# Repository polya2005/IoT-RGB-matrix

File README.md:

# IoT-RGB-matrix

## Functionalities

- Sending custom images (and animations) over WiFi to the display.
- Automatically generate a QR code for display (one application is to rickroll people)
- Serving as a "status" display like date/time, weather, etc.

## Project Components

- 40x40 RGB LED matrix, which is broken down into 25 PCBs of 8x8 matrix
- A control board, which is likely a Raspberry Pi Zero W

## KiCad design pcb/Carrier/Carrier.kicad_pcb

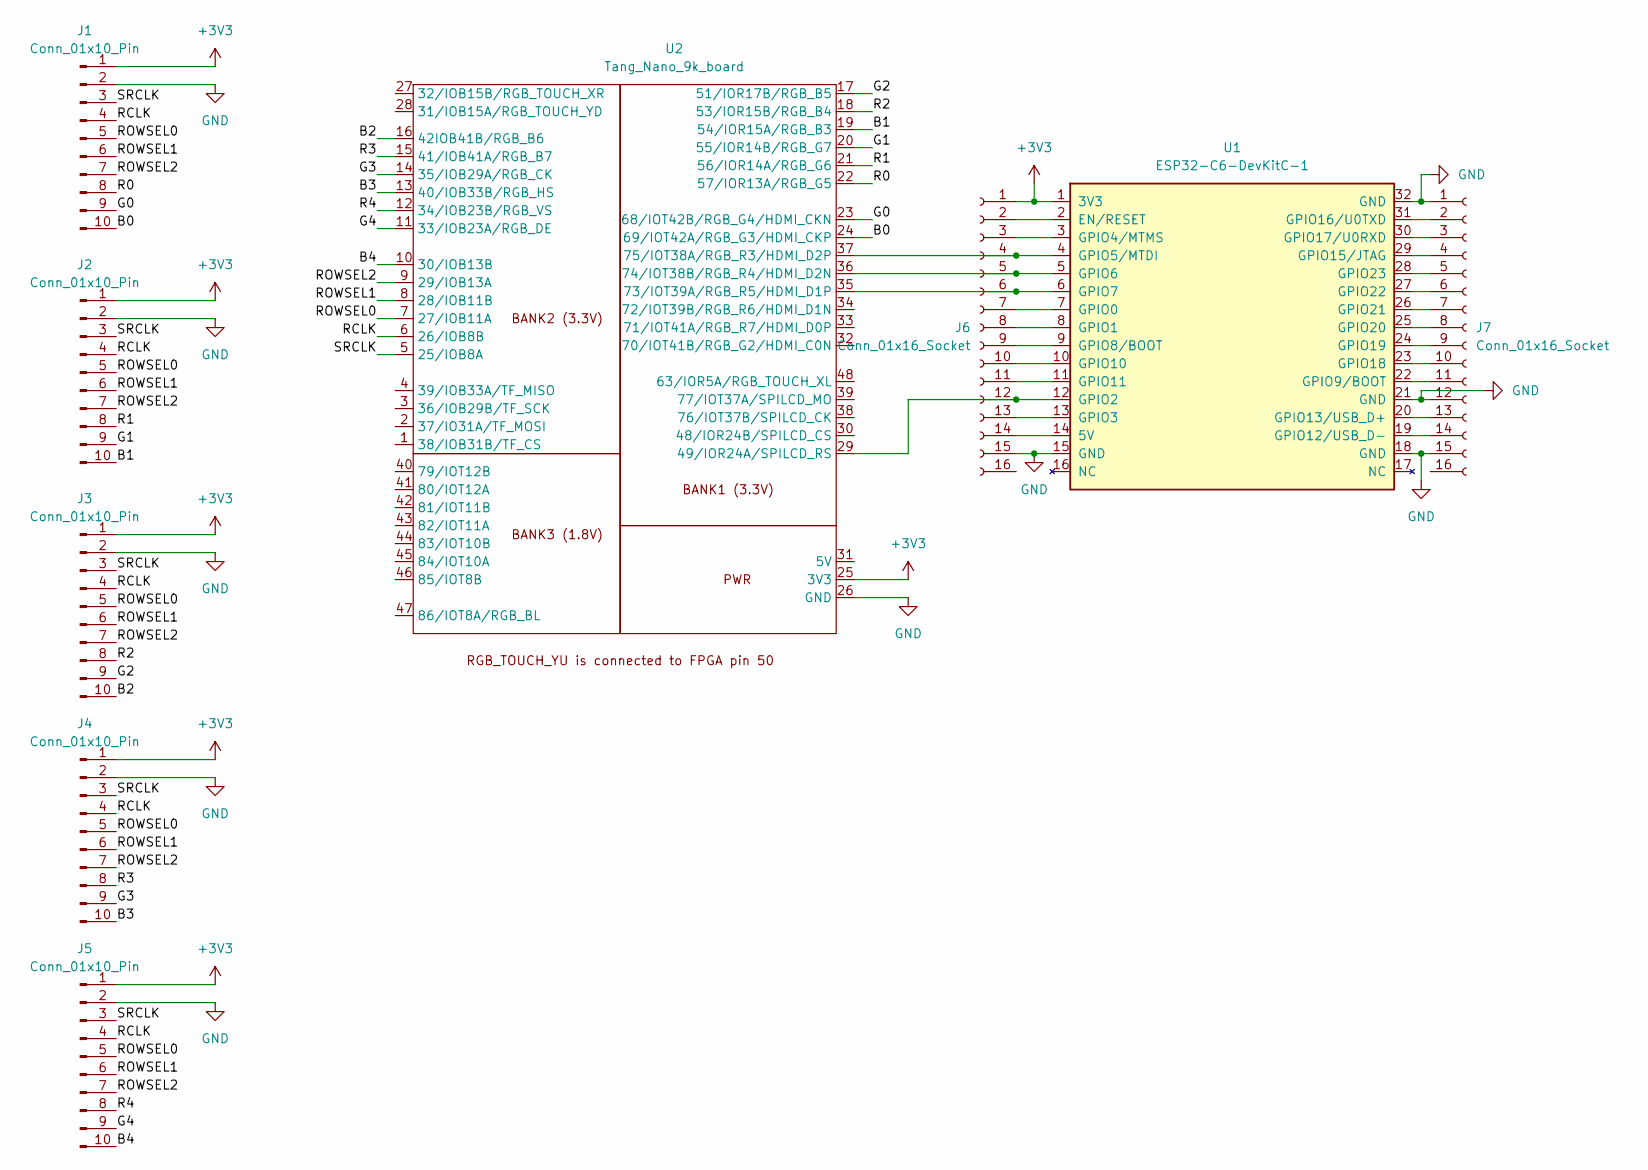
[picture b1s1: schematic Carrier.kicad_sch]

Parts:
J1, J2, J3, J4, J5: Conn_01x10_Pin; PinHeader_1x10_P2.54mm_Vertical
J6, J7: Conn_01x16_Socket; PinSocket_1x16_P2.54mm_Vertical
U1: ESP32-C6-DevKitC-1
U2: Tang_Nano_9k_board; Tang Nano 9K

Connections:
+3V3: J1.1, J2.1, J3.1, J4.1, J5.1, J6.1, U1.1 (3V3), U2.25 (3V3)
/B0: J1.10, U2.24 (69/IOT42A/RGB_G3/HDMI_CKP)
/B1: J2.10, U2.19 (54/IOR15A/RGB_B3)
/B2: J3.10, U2.16 (42IOB41B/RGB_B6)
/B3: J4.10, U2.13 (40/IOB33B/RGB_HS)
/B4: J5.10, U2.10 (30/IOB13B)
/G0: J1.9, U2.23 (68/IOT42B/RGB_G4/HDMI_CKN)
/G1: J2.9, U2.20 (55/IOR14B/RGB_G7)
/G2: J3.9, U2.17 (51/IOR17B/RGB_B5)
/G3: J4.9, U2.14 (35/IOB29A/RGB_CK)
/G4: J5.9, U2.11 (33/IOB23A/RGB_DE)
/R0: J1.8, U2.22 (57/IOR13A/RGB_G5)
/R1: J2.8, U2.21 (56/IOR14A/RGB_G6)
/R2: J3.8, U2.18 (53/IOR15B/RGB_B4)
/R3: J4.8, U2.15 (41/IOB41A/RGB_B7)
/R4: J5.8, U2.12 (34/IOB23B/RGB_VS)
/RCLK: J1.4, J2.4, J3.4, J4.4, J5.4, U2.6 (26/IOB8B)
/ROWSEL0: J1.5, J2.5, J3.5, J4.5, J5.5, U2.7 (27/IOB11A)
/ROWSEL1: J1.6, J2.6, J3.6, J4.6, J5.6, U2.8 (28/IOB11B)
/ROWSEL2: J1.7, J2.7, J3.7, J4.7, J5.7, U2.9 (29/IOB13A)
/SRCLK: J1.3, J2.3, J3.3, J4.3, J5.3, U2.5 (25/IOB8A)
GND: J1.2, J2.2, J3.2, J4.2, J5.2, J6.15, J7.1, J7.12, J7.15, U1.15 (GND), U1.18 (GND), U1.21 (GND), U1.32 (GND), U2.26 (GND)
unnamed: J6.2, U1.2 (EN/RESET)
unnamed: J6.3, U1.3 (GPIO4/MTMS)
unnamed: J6.4, U1.4 (GPIO5/MTDI), U2.37 (75/IOT38A/RGB_R3/HDMI_D2P)
unnamed: J6.5, U1.5 (GPIO6), U2.36 (74/IOT38B/RGB_R4/HDMI_D2N)
unnamed: J6.6, U1.6 (GPIO7), U2.35 (73/IOT39A/RGB_R5/HDMI_D1P)
unnamed: J6.7, U1.7 (GPIO0)
unnamed: J6.8, U1.8 (GPIO1)
unnamed: J6.9, U1.9 (GPIO8/BOOT)
unnamed: J6.10, U1.10 (GPIO10)
unnamed: J6.11, U1.11 (GPIO11)
unnamed: J6.12, U1.12 (GPIO2), U2.29 (49/IOR24A/SPILCD_RS)
unnamed: J6.13, U1.13 (GPIO3)
unnamed: J6.14, U1.14 (5V)
unnamed: J7.2, U1.31 (GPIO16/U0TXD)
unnamed: J7.3, U1.30 (GPIO17/U0RXD)
unnamed: J7.4, U1.29 (GPIO15/JTAG)
unnamed: J7.5, U1.28 (GPIO23)
unnamed: J7.6, U1.27 (GPIO22)
unnamed: J7.7, U1.26 (GPIO21)
unnamed: J7.8, U1.25 (GPIO20)
unnamed: J7.9, U1.24 (GPIO19)
unnamed: J7.10, U1.23 (GPIO18)
unnamed: J7.11, U1.22 (GPIO9/BOOT)
unnamed: J7.13, U1.20 (GPIO13/USB_D+)
unnamed: J7.14, U1.19 (GPIO12/USB_D-)

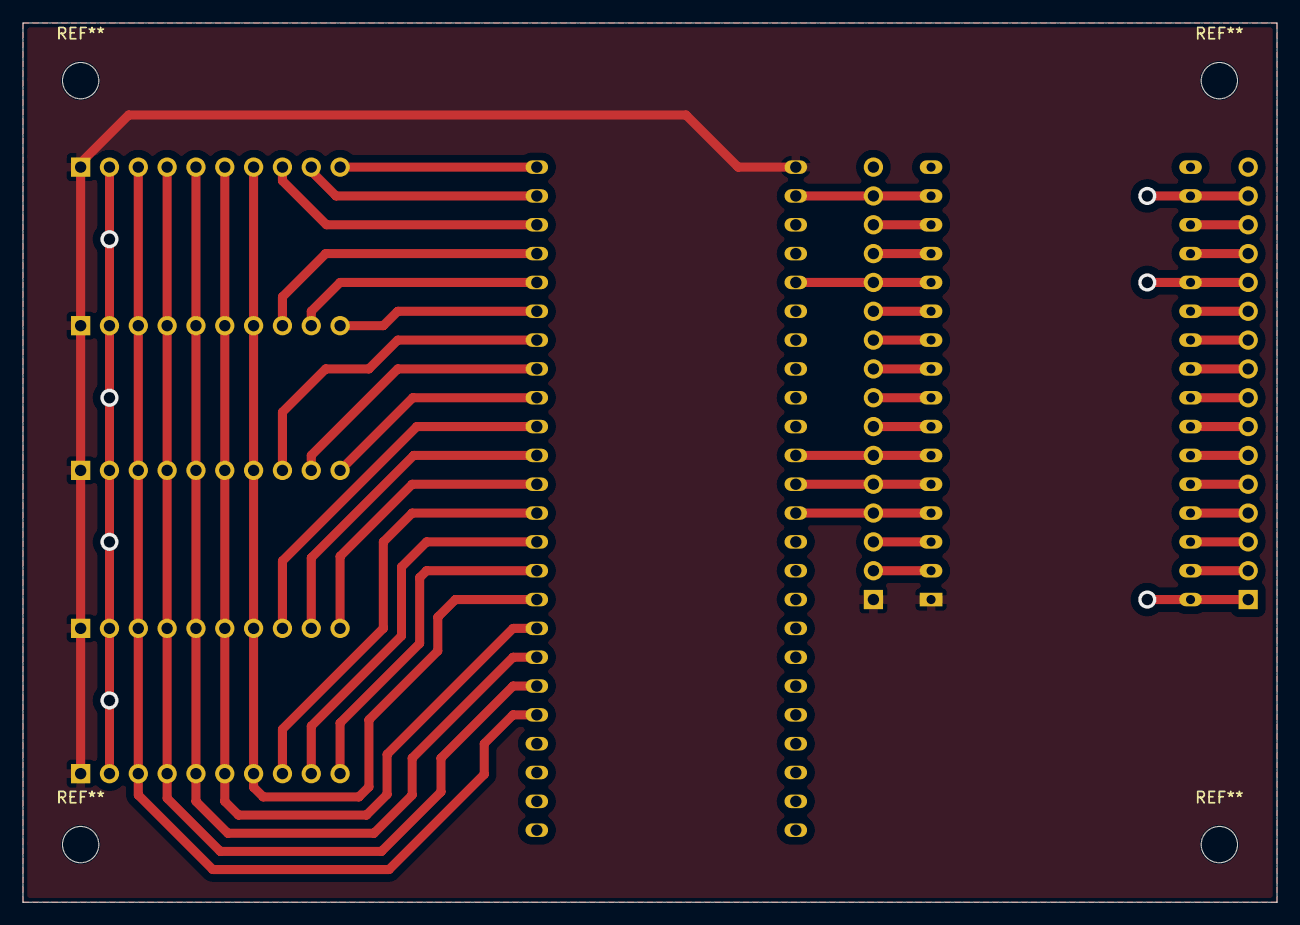
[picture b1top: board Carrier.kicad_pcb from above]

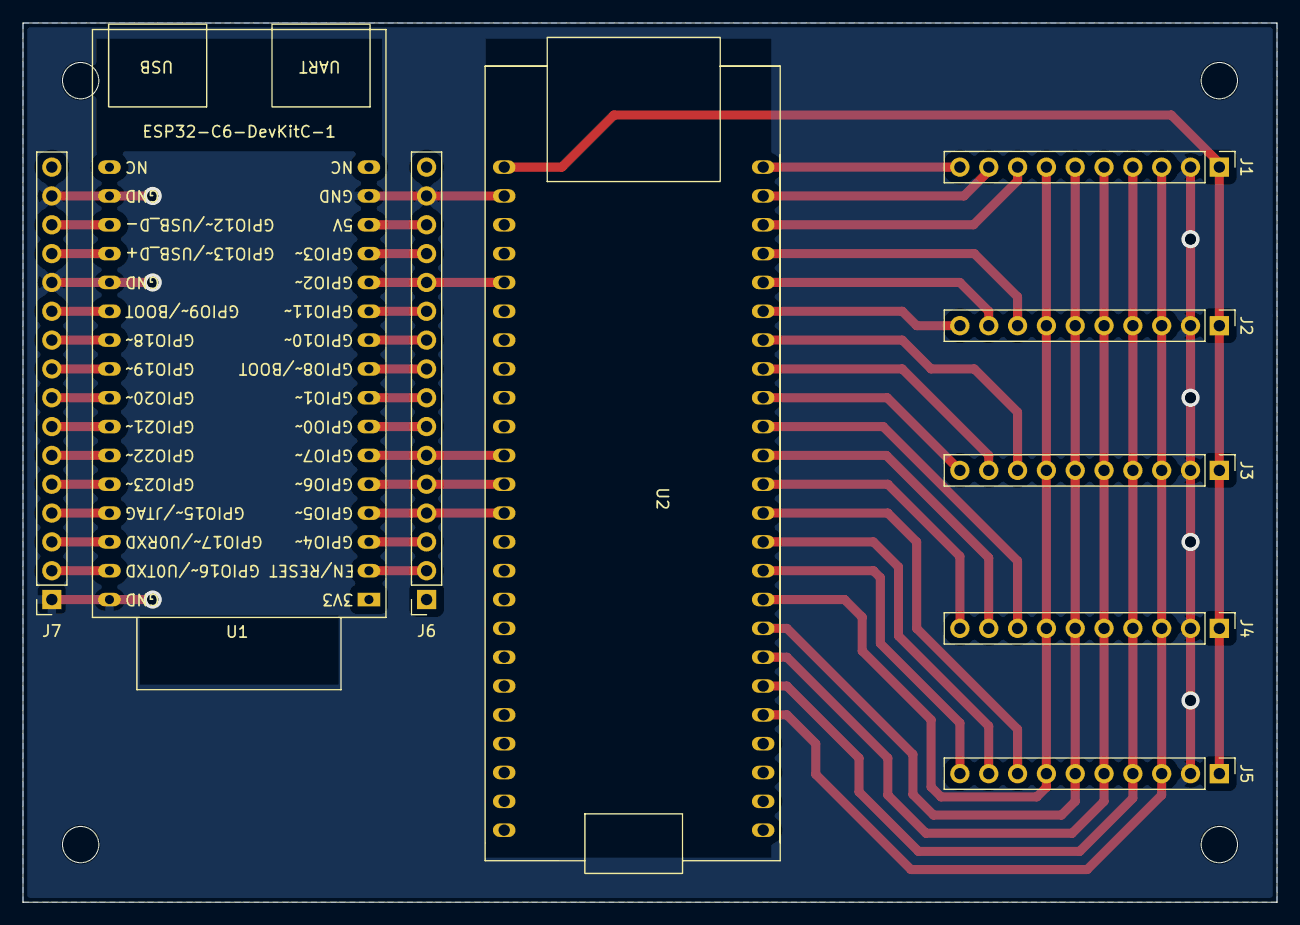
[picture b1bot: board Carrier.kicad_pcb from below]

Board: 2 copper layers, 110.5 x 77.5 mm, 9 parts (9 on the bottom side), 47 nets.

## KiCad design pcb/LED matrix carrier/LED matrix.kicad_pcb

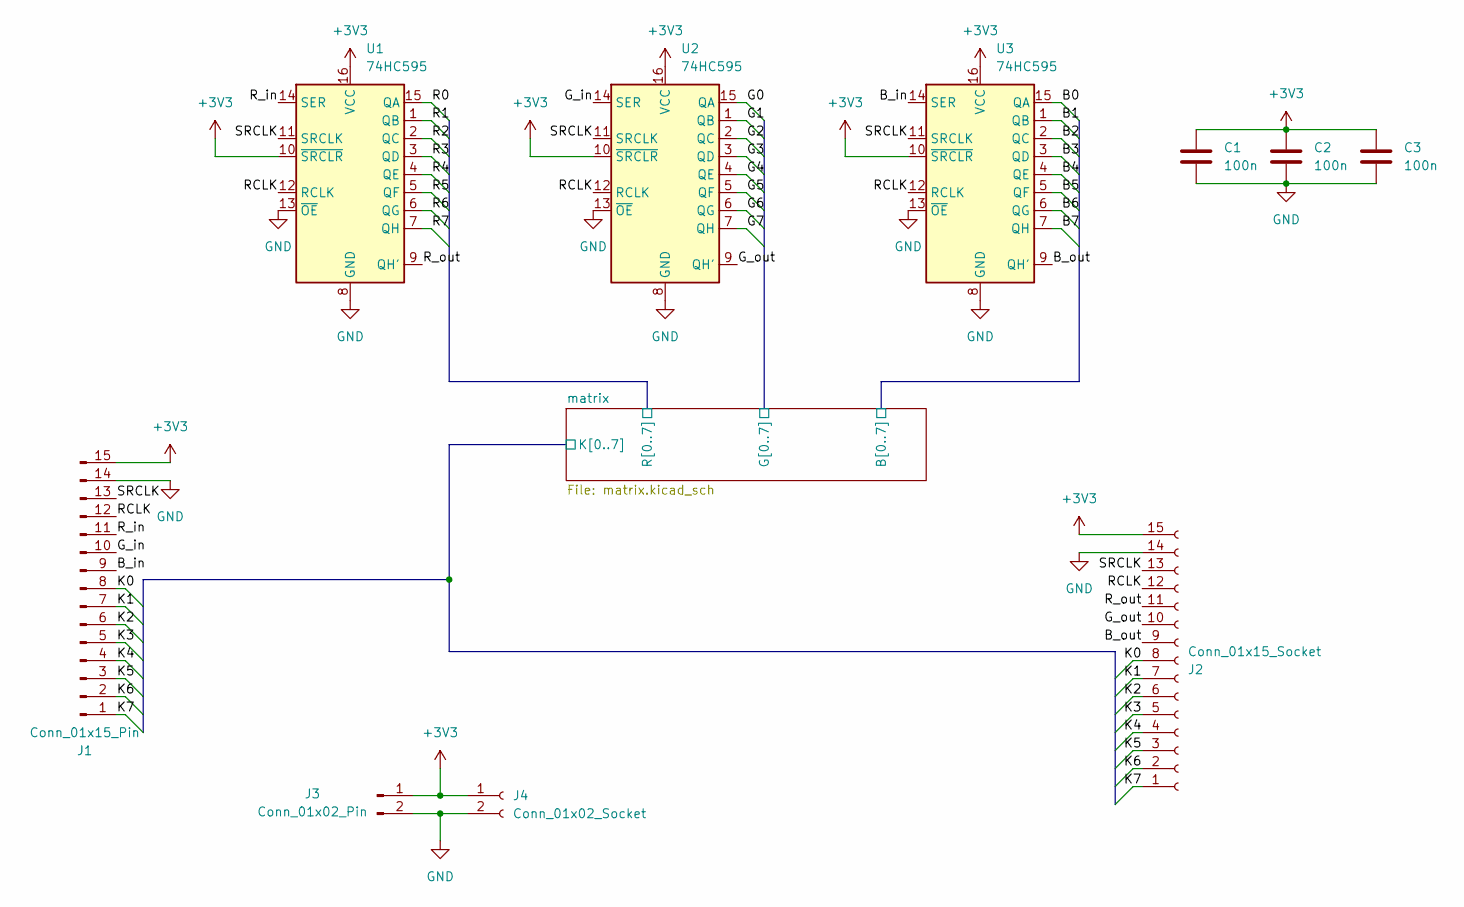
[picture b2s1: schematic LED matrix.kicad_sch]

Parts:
C1, C2, C3: 100n; C_1206_3216Metric_Pad1.33x1.80mm_HandSolder
J1: Conn_01x15_Pin; PinHeader_1x15_P2.54mm_Horizontal
J2: Conn_01x15_Socket; PinSocket_1x15_P2.54mm_Horizontal
J3: Conn_01x02_Pin; PinHeader_1x02_P2.54mm_Horizontal
J4: Conn_01x02_Socket; PinSocket_1x02_P2.54mm_Horizontal
U1, U2, U3: 74HC595; TSSOP-16_4.4x5mm_P0.65mm

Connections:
+3V3: C1.1, C2.1, C3.1, J1.15, J2.15, J3.1, J4.1, U1.10 (~SRCLR), U1.16 (VCC), U2.10 (~SRCLR), U2.16 (VCC), U3.10 (~SRCLR), U3.16 (VCC)
/B_in: J1.9, U3.14 (SER)
/B_out: J2.9, U3.9 (QH')
/G_in: J1.10, U2.14 (SER)
/G_out: J2.10, U2.9 (QH')
/RCLK: J1.12, J2.12, U1.12 (RCLK), U2.12 (RCLK), U3.12 (RCLK)
/R_in: J1.11, U1.14 (SER)
/R_out: J2.11, U1.9 (QH')
/SRCLK: J1.13, J2.13, U1.11 (SRCLK), U2.11 (SRCLK), U3.11 (SRCLK)
/matrix/B0: U3.15 (QA); also elsewhere on the board
/matrix/B1: U3.1 (QB); also elsewhere on the board
/matrix/B2: U3.2 (QC); also elsewhere on the board
/matrix/B3: U3.3 (QD); also elsewhere on the board
/matrix/B4: U3.4 (QE); also elsewhere on the board
/matrix/B5: U3.5 (QF); also elsewhere on the board
/matrix/B6: U3.6 (QG); also elsewhere on the board
/matrix/B7: U3.7 (QH); also elsewhere on the board
/matrix/G0: U2.15 (QA); also elsewhere on the board
/matrix/G1: U2.1 (QB); also elsewhere on the board
/matrix/G2: U2.2 (QC); also elsewhere on the board
/matrix/G3: U2.3 (QD); also elsewhere on the board
/matrix/G4: U2.4 (QE); also elsewhere on the board
/matrix/G5: U2.5 (QF); also elsewhere on the board
/matrix/G6: U2.6 (QG); also elsewhere on the board
/matrix/G7: U2.7 (QH); also elsewhere on the board
/matrix/K0: J1.8, J2.8; also elsewhere on the board
/matrix/K1: J1.7, J2.7; also elsewhere on the board
/matrix/K2: J1.6, J2.6; also elsewhere on the board
/matrix/K3: J1.5, J2.5; also elsewhere on the board
/matrix/K4: J1.4, J2.4; also elsewhere on the board
/matrix/K5: J1.3, J2.3; also elsewhere on the board
/matrix/K6: J1.2, J2.2; also elsewhere on the board
/matrix/K7: J1.1, J2.1; also elsewhere on the board
/matrix/R0: U1.15 (QA); also elsewhere on the board
/matrix/R1: U1.1 (QB); also elsewhere on the board
/matrix/R2: U1.2 (QC); also elsewhere on the board
/matrix/R3: U1.3 (QD); also elsewhere on the board
/matrix/R4: U1.4 (QE); also elsewhere on the board
/matrix/R5: U1.5 (QF); also elsewhere on the board
/matrix/R6: U1.6 (QG); also elsewhere on the board
/matrix/R7: U1.7 (QH); also elsewhere on the board
GND: C1.2, C2.2, C3.2, J1.14, J2.14, J3.2, J4.2, U1.8 (GND), U1.13 (~OE), U2.8 (GND), U2.13 (~OE), U3.8 (GND), U3.13 (~OE)

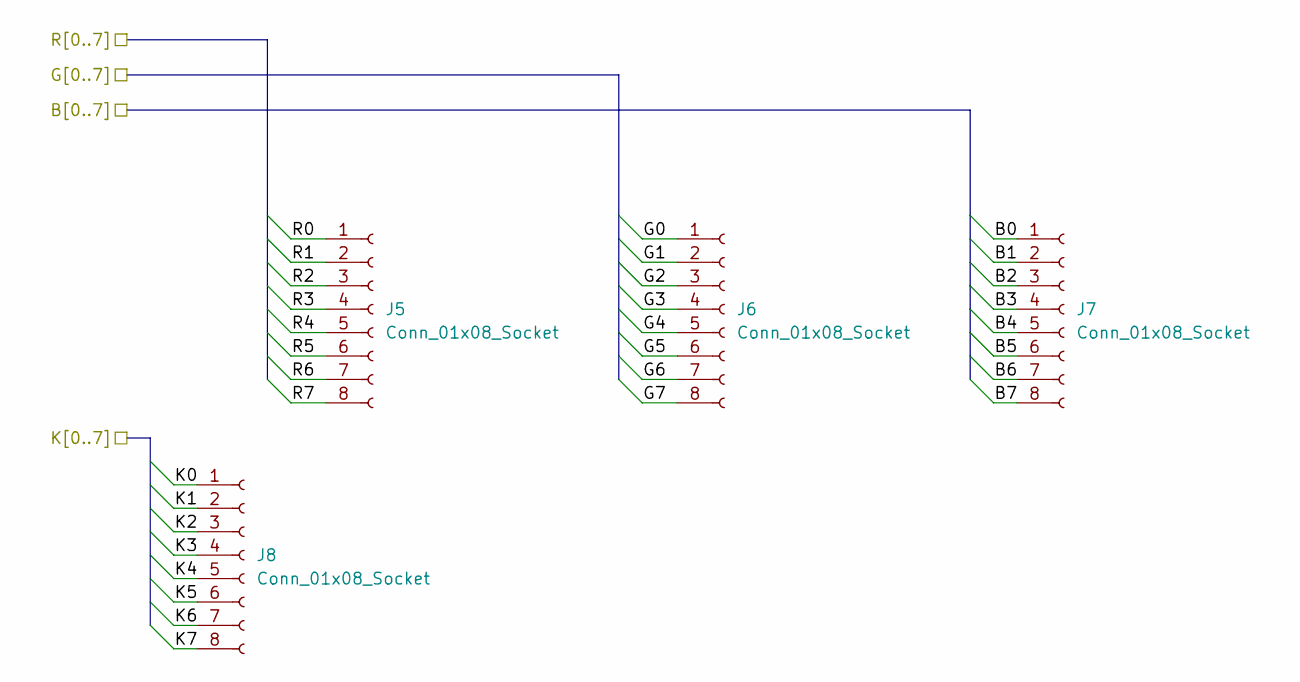
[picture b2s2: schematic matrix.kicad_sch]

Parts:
J5, J6, J7, J8: Conn_01x08_Socket; PinSocket_1x08_P2.54mm_Vertical

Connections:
/matrix/B0: J7.1; also elsewhere on the board
/matrix/B1: J7.2; also elsewhere on the board
/matrix/B2: J7.3; also elsewhere on the board
/matrix/B3: J7.4; also elsewhere on the board
/matrix/B4: J7.5; also elsewhere on the board
/matrix/B5: J7.6; also elsewhere on the board
/matrix/B6: J7.7; also elsewhere on the board
/matrix/B7: J7.8; also elsewhere on the board
/matrix/G0: J6.1; also elsewhere on the board
/matrix/G1: J6.2; also elsewhere on the board
/matrix/G2: J6.3; also elsewhere on the board
/matrix/G3: J6.4; also elsewhere on the board
/matrix/G4: J6.5; also elsewhere on the board
/matrix/G5: J6.6; also elsewhere on the board
/matrix/G6: J6.7; also elsewhere on the board
/matrix/G7: J6.8; also elsewhere on the board
/matrix/K0: J8.1; also elsewhere on the board
/matrix/K1: J8.2; also elsewhere on the board
/matrix/K2: J8.3; also elsewhere on the board
/matrix/K3: J8.4; also elsewhere on the board
/matrix/K4: J8.5; also elsewhere on the board
/matrix/K5: J8.6; also elsewhere on the board
/matrix/K6: J8.7; also elsewhere on the board
/matrix/K7: J8.8; also elsewhere on the board
/matrix/R0: J5.1; also elsewhere on the board
/matrix/R1: J5.2; also elsewhere on the board
/matrix/R2: J5.3; also elsewhere on the board
/matrix/R3: J5.4; also elsewhere on the board
/matrix/R4: J5.5; also elsewhere on the board
/matrix/R5: J5.6; also elsewhere on the board
/matrix/R6: J5.7; also elsewhere on the board
/matrix/R7: J5.8; also elsewhere on the board

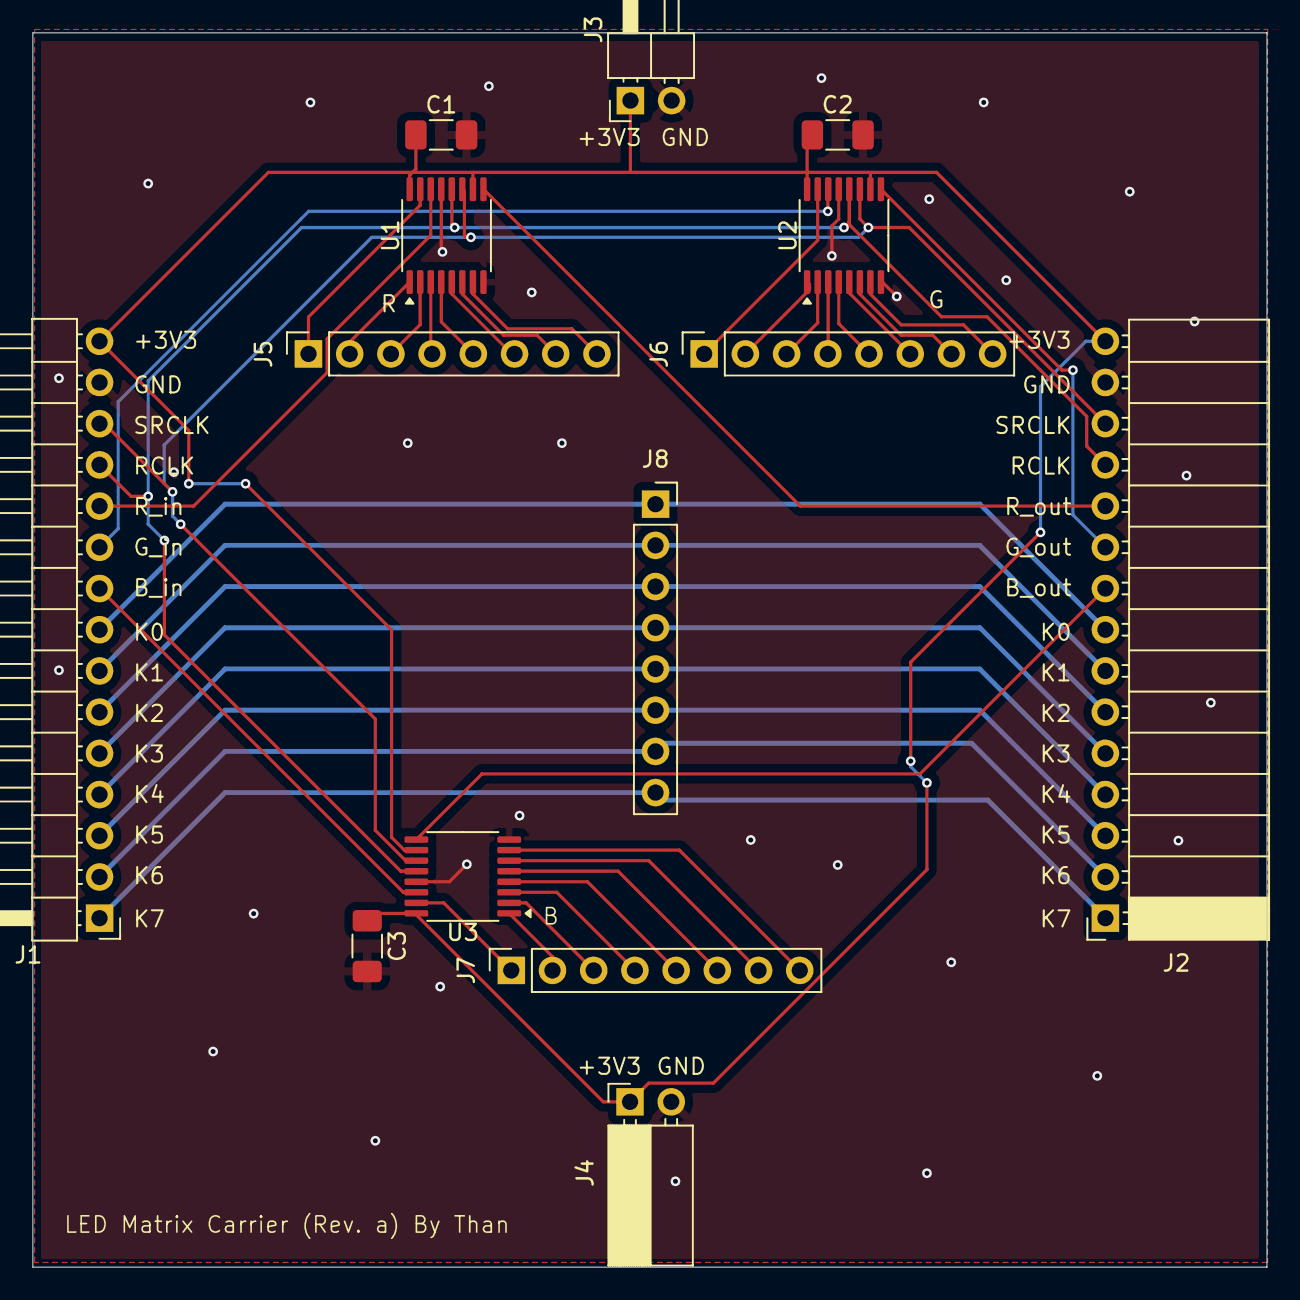
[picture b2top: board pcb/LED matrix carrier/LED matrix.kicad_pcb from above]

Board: 2 copper layers, 76.1 x 76.1 mm, 14 parts (0 on the bottom side), 42 nets.

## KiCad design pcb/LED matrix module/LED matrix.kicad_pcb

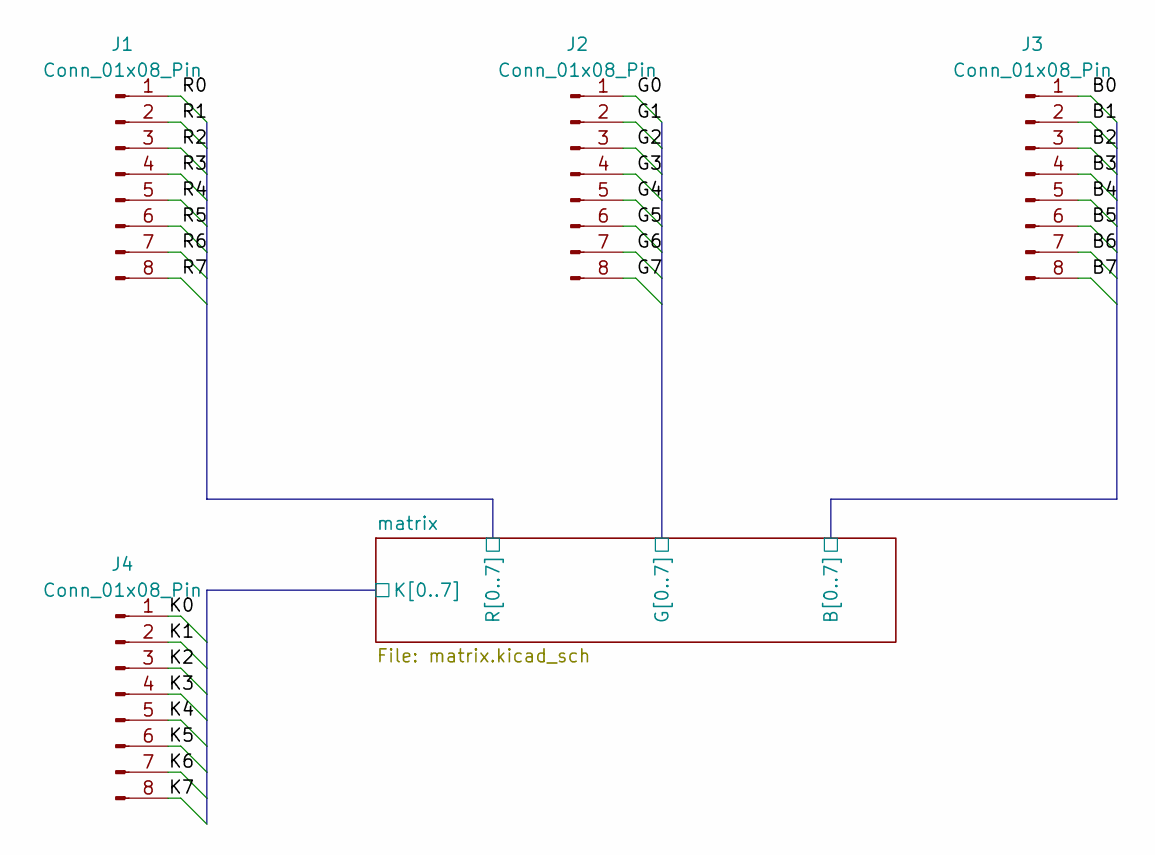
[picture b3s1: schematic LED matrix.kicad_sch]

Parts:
J1, J2, J3, J4: Conn_01x08_Pin; PinHeader_1x08_P2.54mm_Vertical

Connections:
/matrix/B0: J3.1; also elsewhere on the board
/matrix/B1: J3.2; also elsewhere on the board
/matrix/B2: J3.3; also elsewhere on the board
/matrix/B3: J3.4; also elsewhere on the board
/matrix/B4: J3.5; also elsewhere on the board
/matrix/B5: J3.6; also elsewhere on the board
/matrix/B6: J3.7; also elsewhere on the board
/matrix/B7: J3.8; also elsewhere on the board
/matrix/G0: J2.1; also elsewhere on the board
/matrix/G1: J2.2; also elsewhere on the board
/matrix/G2: J2.3; also elsewhere on the board
/matrix/G3: J2.4; also elsewhere on the board
/matrix/G4: J2.5; also elsewhere on the board
/matrix/G5: J2.6; also elsewhere on the board
/matrix/G6: J2.7; also elsewhere on the board
/matrix/G7: J2.8; also elsewhere on the board
/matrix/K0: J4.1; also elsewhere on the board
/matrix/K1: J4.2; also elsewhere on the board
/matrix/K2: J4.3; also elsewhere on the board
/matrix/K3: J4.4; also elsewhere on the board
/matrix/K4: J4.5; also elsewhere on the board
/matrix/K5: J4.6; also elsewhere on the board
/matrix/K6: J4.7; also elsewhere on the board
/matrix/K7: J4.8; also elsewhere on the board
/matrix/R0: J1.1; also elsewhere on the board
/matrix/R1: J1.2; also elsewhere on the board
/matrix/R2: J1.3; also elsewhere on the board
/matrix/R3: J1.4; also elsewhere on the board
/matrix/R4: J1.5; also elsewhere on the board
/matrix/R5: J1.6; also elsewhere on the board
/matrix/R6: J1.7; also elsewhere on the board
/matrix/R7: J1.8; also elsewhere on the board

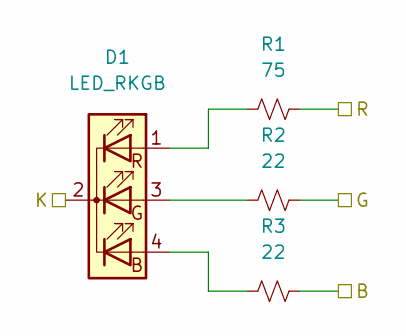
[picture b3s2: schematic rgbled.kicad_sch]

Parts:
D1: LED_RKGB; LED_D5.0mm-4_RGB
R1: 75; R_0402_1005Metric; LCSC C25133
R2, R3: 22; R_0402_1005Metric; LCSC C25092

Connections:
/matrix/B0: R3.2; also elsewhere on the board
/matrix/G0: R2.2; also elsewhere on the board
/matrix/K0: D1.2 (K); also elsewhere on the board
/matrix/R0: R1.2; also elsewhere on the board
unnamed: D1.4 (BA), R3.1
unnamed: D1.3 (GA), R2.1
unnamed: D1.1 (RA), R1.1

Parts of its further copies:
D2, D3, D4, D5, D6, D7, D8, D9, D10, D11, D12, D13, D14, D15, D16, D17, D18, D19, D20, D21, D22, D23, D24, D25, D26, D27, D28, D29, D30, D31, D32, D33, D34, D35, D36, D37, D38, D39, D40, D41, D42, D43, D44, D45, D46, D47, D48, D49, D50, D51, D52, D53, D54, D55, D56, D57, D58, D59, D60, D61, D62, D63, D64: LED_RKGB; LED_D5.0mm-4_RGB
R4, R7, R10, R13, R16, R19, R22, R25, R28, R31, R34, R37, R40, R43, R46, R49, R52, R55, R58, R61, R64, R67, R70, R73, R76, R79, R82, R85, R88, R91, R94, R97, R100, R103, R106, R109, R112, R115, R118, R121, R124, R127, R130, R133, R136, R139, R142, R145, R148, R151, R154, R157, R160, R163, R166, R169, R172, R175, R178, R181, R184, R187, R190: 75; R_0402_1005Metric; LCSC C25133
R5, R6, R8, R9, R11, R12, R14, R15, R17, R18, R20, R21, R23, R24, R26, R27, R29, R30, R32, R33, R35, R36, R38, R39, R41, R42, R44, R45, R47, R48, R50, R51, R53, R54, R56, R57, R59, R60, R62, R63, R65, R66, R68, R69, R71, R72, R74, R75, R77, R78, R80, R81, R83, R84, R86, R87, R89, R90, R92, R93, R95, R96, R98, R99, R101, R102, R104, R105, R107, R108, R110, R111, R113, R114, R116, R117, R119, R120, R122, R123, R125, R126, R128, R129, R131, R132, R134, R135, R137, R138, R140, R141, R143, R144, R146, R147, R149, R150, R152, R153, R155, R156, R158, R159, R161, R162, R164, R165, R167, R168, R170, R171, R173, R174, R176, R177, R179, R180, R182, R183, R185, R186, R188, R189, R191, R192: 22; R_0402_1005Metric; LCSC C25092

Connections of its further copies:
/matrix/B0: R6.2, R9.2, R12.2, R15.2, R18.2, R21.2, R24.2; also elsewhere on the board
/matrix/B1: R27.2, R30.2, R33.2, R36.2, R39.2, R42.2, R45.2, R48.2; also elsewhere on the board
/matrix/B2: R51.2, R54.2, R57.2, R60.2, R63.2, R66.2, R69.2, R72.2; also elsewhere on the board
/matrix/B3: R75.2, R78.2, R81.2, R84.2, R87.2, R90.2, R93.2, R96.2; also elsewhere on the board
/matrix/B4: R99.2, R102.2, R105.2, R108.2, R111.2, R114.2, R117.2, R120.2; also elsewhere on the board
/matrix/B5: R123.2, R126.2, R129.2, R132.2, R135.2, R138.2, R141.2, R144.2; also elsewhere on the board
/matrix/B6: R147.2, R150.2, R153.2, R156.2, R159.2, R162.2, R165.2, R168.2; also elsewhere on the board
/matrix/B7: R171.2, R174.2, R177.2, R180.2, R183.2, R186.2, R189.2, R192.2; also elsewhere on the board
/matrix/G0: R5.2, R8.2, R11.2, R14.2, R17.2, R20.2, R23.2; also elsewhere on the board
/matrix/G1: R26.2, R29.2, R32.2, R35.2, R38.2, R41.2, R44.2, R47.2; also elsewhere on the board
/matrix/G2: R50.2, R53.2, R56.2, R59.2, R62.2, R65.2, R68.2, R71.2; also elsewhere on the board
/matrix/G3: R74.2, R77.2, R80.2, R83.2, R86.2, R89.2, R92.2, R95.2; also elsewhere on the board
/matrix/G4: R98.2, R101.2, R104.2, R107.2, R110.2, R113.2, R116.2, R119.2; also elsewhere on the board
/matrix/G5: R122.2, R125.2, R128.2, R131.2, R134.2, R137.2, R140.2, R143.2; also elsewhere on the board
/matrix/G6: R146.2, R149.2, R152.2, R155.2, R158.2, R161.2, R164.2, R167.2; also elsewhere on the board
/matrix/G7: R170.2, R173.2, R176.2, R179.2, R182.2, R185.2, R188.2, R191.2; also elsewhere on the board
/matrix/K0: D9.2 (K), D17.2 (K), D25.2 (K), D33.2 (K), D41.2 (K), D49.2 (K), D57.2 (K); also elsewhere on the board
/matrix/K1: D2.2 (K), D10.2 (K), D18.2 (K), D26.2 (K), D34.2 (K), D42.2 (K), D50.2 (K), D58.2 (K); also elsewhere on the board
/matrix/K2: D3.2 (K), D11.2 (K), D19.2 (K), D27.2 (K), D35.2 (K), D43.2 (K), D51.2 (K), D59.2 (K); also elsewhere on the board
/matrix/K3: D4.2 (K), D12.2 (K), D20.2 (K), D28.2 (K), D36.2 (K), D44.2 (K), D52.2 (K), D60.2 (K); also elsewhere on the board
/matrix/K4: D5.2 (K), D13.2 (K), D21.2 (K), D29.2 (K), D37.2 (K), D45.2 (K), D53.2 (K), D61.2 (K); also elsewhere on the board
/matrix/K5: D6.2 (K), D14.2 (K), D22.2 (K), D30.2 (K), D38.2 (K), D46.2 (K), D54.2 (K), D62.2 (K); also elsewhere on the board
/matrix/K6: D7.2 (K), D15.2 (K), D23.2 (K), D31.2 (K), D39.2 (K), D47.2 (K), D55.2 (K), D63.2 (K); also elsewhere on the board
/matrix/K7: D8.2 (K), D16.2 (K), D24.2 (K), D32.2 (K), D40.2 (K), D48.2 (K), D56.2 (K), D64.2 (K); also elsewhere on the board
/matrix/R0: R4.2, R7.2, R10.2, R13.2, R16.2, R19.2, R22.2; also elsewhere on the board
/matrix/R1: R25.2, R28.2, R31.2, R34.2, R37.2, R40.2, R43.2, R46.2; also elsewhere on the board
/matrix/R2: R49.2, R52.2, R55.2, R58.2, R61.2, R64.2, R67.2, R70.2; also elsewhere on the board
/matrix/R3: R73.2, R76.2, R79.2, R82.2, R85.2, R88.2, R91.2, R94.2; also elsewhere on the board
/matrix/R4: R97.2, R100.2, R103.2, R106.2, R109.2, R112.2, R115.2, R118.2; also elsewhere on the board
/matrix/R5: R121.2, R124.2, R127.2, R130.2, R133.2, R136.2, R139.2, R142.2; also elsewhere on the board
/matrix/R6: R145.2, R148.2, R151.2, R154.2, R157.2, R160.2, R163.2, R166.2; also elsewhere on the board
/matrix/R7: R169.2, R172.2, R175.2, R178.2, R181.2, R184.2, R187.2, R190.2; also elsewhere on the board
unnamed: D2.4 (BA), R6.1
unnamed: D2.3 (GA), R5.1
unnamed: D2.1 (RA), R4.1
unnamed: D3.4 (BA), R9.1
unnamed: D3.3 (GA), R8.1
unnamed: D3.1 (RA), R7.1
unnamed: D4.4 (BA), R12.1
unnamed: D4.3 (GA), R11.1
unnamed: D4.1 (RA), R10.1
unnamed: D5.4 (BA), R15.1
unnamed: D5.3 (GA), R14.1
unnamed: D5.1 (RA), R13.1
unnamed: D6.4 (BA), R18.1
unnamed: D6.3 (GA), R17.1
unnamed: D6.1 (RA), R16.1
unnamed: D7.4 (BA), R21.1
unnamed: D7.3 (GA), R20.1
unnamed: D7.1 (RA), R19.1
unnamed: D8.4 (BA), R24.1
unnamed: D8.3 (GA), R23.1
unnamed: D8.1 (RA), R22.1
unnamed: D9.4 (BA), R27.1
unnamed: D9.3 (GA), R26.1
unnamed: D9.1 (RA), R25.1
unnamed: D10.4 (BA), R30.1
unnamed: D10.3 (GA), R29.1
unnamed: D10.1 (RA), R28.1
unnamed: D11.4 (BA), R33.1
unnamed: D11.3 (GA), R32.1
unnamed: D11.1 (RA), R31.1
unnamed: D12.4 (BA), R36.1
unnamed: D12.3 (GA), R35.1
unnamed: D12.1 (RA), R34.1
unnamed: D13.4 (BA), R39.1
unnamed: D13.3 (GA), R38.1
unnamed: D13.1 (RA), R37.1
unnamed: D14.4 (BA), R42.1
unnamed: D14.3 (GA), R41.1
unnamed: D14.1 (RA), R40.1
unnamed: D15.4 (BA), R45.1
unnamed: D15.3 (GA), R44.1
unnamed: D15.1 (RA), R43.1
unnamed: D16.4 (BA), R48.1
unnamed: D16.3 (GA), R47.1
unnamed: D16.1 (RA), R46.1
unnamed: D17.4 (BA), R51.1
unnamed: D17.3 (GA), R50.1
unnamed: D17.1 (RA), R49.1
unnamed: D18.4 (BA), R54.1
unnamed: D18.3 (GA), R53.1
unnamed: D18.1 (RA), R52.1
unnamed: D19.4 (BA), R57.1
unnamed: D19.3 (GA), R56.1
unnamed: D19.1 (RA), R55.1
unnamed: D20.4 (BA), R60.1
unnamed: D20.3 (GA), R59.1
unnamed: D20.1 (RA), R58.1
unnamed: D21.4 (BA), R63.1
unnamed: D21.3 (GA), R62.1
unnamed: D21.1 (RA), R61.1
unnamed: D22.4 (BA), R66.1
unnamed: D22.3 (GA), R65.1
unnamed: D22.1 (RA), R64.1
unnamed: D23.4 (BA), R69.1
unnamed: D23.3 (GA), R68.1
unnamed: D23.1 (RA), R67.1
unnamed: D24.4 (BA), R72.1
unnamed: D24.3 (GA), R71.1
unnamed: D24.1 (RA), R70.1
unnamed: D25.4 (BA), R75.1
unnamed: D25.3 (GA), R74.1
unnamed: D25.1 (RA), R73.1
unnamed: D26.4 (BA), R78.1
unnamed: D26.3 (GA), R77.1
unnamed: D26.1 (RA), R76.1
unnamed: D27.4 (BA), R81.1
unnamed: D27.3 (GA), R80.1
unnamed: D27.1 (RA), R79.1
unnamed: D28.4 (BA), R84.1
unnamed: D28.3 (GA), R83.1
unnamed: D28.1 (RA), R82.1
unnamed: D29.4 (BA), R87.1
unnamed: D29.3 (GA), R86.1
unnamed: D29.1 (RA), R85.1
unnamed: D30.4 (BA), R90.1
unnamed: D30.3 (GA), R89.1
unnamed: D30.1 (RA), R88.1
unnamed: D31.4 (BA), R93.1
unnamed: D31.3 (GA), R92.1
unnamed: D31.1 (RA), R91.1
unnamed: D32.4 (BA), R96.1
unnamed: D32.3 (GA), R95.1
unnamed: D32.1 (RA), R94.1
unnamed: D33.4 (BA), R99.1
unnamed: D33.3 (GA), R98.1
unnamed: D33.1 (RA), R97.1
unnamed: D34.4 (BA), R102.1
unnamed: D34.3 (GA), R101.1
unnamed: D34.1 (RA), R100.1
unnamed: D35.4 (BA), R105.1
unnamed: D35.3 (GA), R104.1
unnamed: D35.1 (RA), R103.1
unnamed: D36.4 (BA), R108.1
unnamed: D36.3 (GA), R107.1
unnamed: D36.1 (RA), R106.1
unnamed: D37.4 (BA), R111.1
unnamed: D37.3 (GA), R110.1
unnamed: D37.1 (RA), R109.1
unnamed: D38.4 (BA), R114.1
unnamed: D38.3 (GA), R113.1
unnamed: D38.1 (RA), R112.1
unnamed: D39.4 (BA), R117.1
unnamed: D39.3 (GA), R116.1
unnamed: D39.1 (RA), R115.1
unnamed: D40.4 (BA), R120.1
unnamed: D40.3 (GA), R119.1
unnamed: D40.1 (RA), R118.1
unnamed: D41.4 (BA), R123.1
unnamed: D41.3 (GA), R122.1
unnamed: D41.1 (RA), R121.1
unnamed: D42.4 (BA), R126.1
unnamed: D42.3 (GA), R125.1
unnamed: D42.1 (RA), R124.1
unnamed: D43.4 (BA), R129.1
unnamed: D43.3 (GA), R128.1
unnamed: D43.1 (RA), R127.1
unnamed: D44.4 (BA), R132.1
unnamed: D44.3 (GA), R131.1
unnamed: D44.1 (RA), R130.1
unnamed: D45.4 (BA), R135.1
unnamed: D45.3 (GA), R134.1
unnamed: D45.1 (RA), R133.1
unnamed: D46.4 (BA), R138.1
unnamed: D46.3 (GA), R137.1
unnamed: D46.1 (RA), R136.1
unnamed: D47.4 (BA), R141.1
unnamed: D47.3 (GA), R140.1
unnamed: D47.1 (RA), R139.1
unnamed: D48.4 (BA), R144.1
unnamed: D48.3 (GA), R143.1
unnamed: D48.1 (RA), R142.1
unnamed: D49.4 (BA), R147.1
unnamed: D49.3 (GA), R146.1
unnamed: D49.1 (RA), R145.1
unnamed: D50.4 (BA), R150.1
unnamed: D50.3 (GA), R149.1
unnamed: D50.1 (RA), R148.1
unnamed: D51.4 (BA), R153.1
unnamed: D51.3 (GA), R152.1
unnamed: D51.1 (RA), R151.1
unnamed: D52.4 (BA), R156.1
unnamed: D52.3 (GA), R155.1
unnamed: D52.1 (RA), R154.1
unnamed: D53.4 (BA), R159.1
unnamed: D53.3 (GA), R158.1
unnamed: D53.1 (RA), R157.1
unnamed: D54.4 (BA), R162.1
unnamed: D54.3 (GA), R161.1
unnamed: D54.1 (RA), R160.1
unnamed: D55.4 (BA), R165.1
unnamed: D55.3 (GA), R164.1
unnamed: D55.1 (RA), R163.1
unnamed: D56.4 (BA), R168.1
unnamed: D56.3 (GA), R167.1
unnamed: D56.1 (RA), R166.1
unnamed: D57.4 (BA), R171.1
unnamed: D57.3 (GA), R170.1
unnamed: D57.1 (RA), R169.1
unnamed: D58.4 (BA), R174.1
unnamed: D58.3 (GA), R173.1
unnamed: D58.1 (RA), R172.1
unnamed: D59.4 (BA), R177.1
unnamed: D59.3 (GA), R176.1
unnamed: D59.1 (RA), R175.1
unnamed: D60.4 (BA), R180.1
unnamed: D60.3 (GA), R179.1
unnamed: D60.1 (RA), R178.1
unnamed: D61.4 (BA), R183.1
unnamed: D61.3 (GA), R182.1
unnamed: D61.1 (RA), R181.1
unnamed: D62.4 (BA), R186.1
unnamed: D62.3 (GA), R185.1
unnamed: D62.1 (RA), R184.1
unnamed: D63.4 (BA), R189.1
unnamed: D63.3 (GA), R188.1
unnamed: D63.1 (RA), R187.1
unnamed: D64.4 (BA), R192.1
unnamed: D64.3 (GA), R191.1
unnamed: D64.1 (RA), R190.1
